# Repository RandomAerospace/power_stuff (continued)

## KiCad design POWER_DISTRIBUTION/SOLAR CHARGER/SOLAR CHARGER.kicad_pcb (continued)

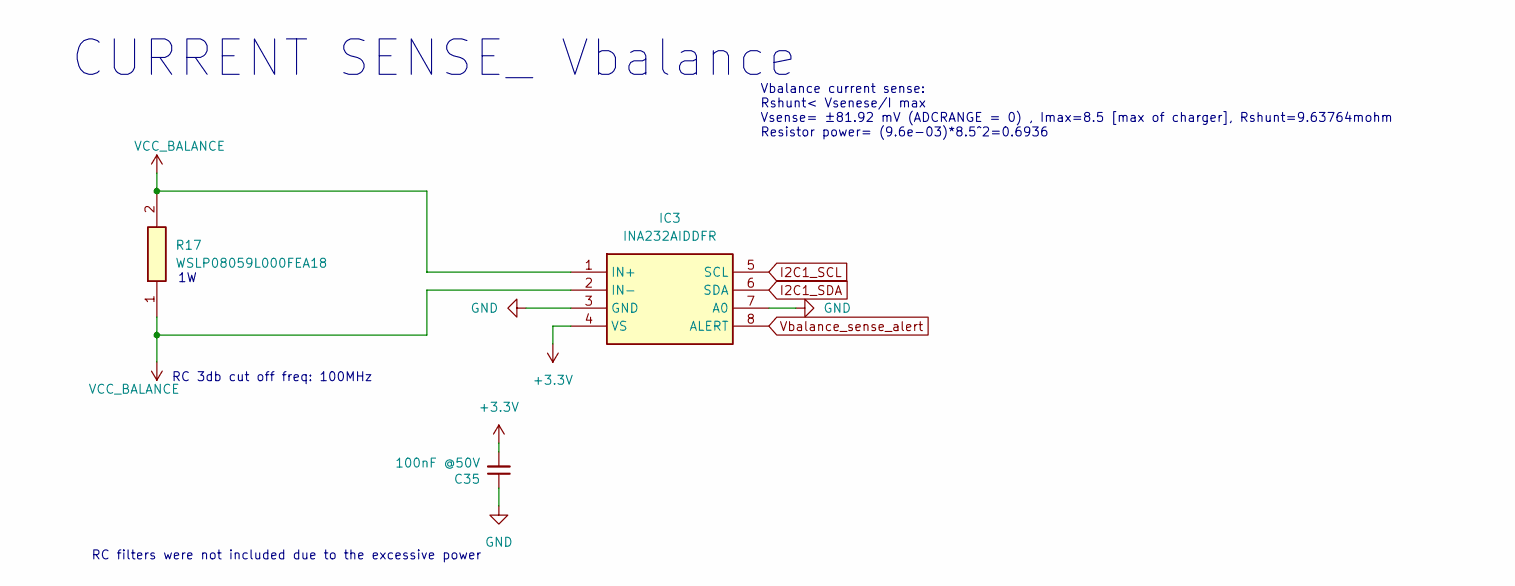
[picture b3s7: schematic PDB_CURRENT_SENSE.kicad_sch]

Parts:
C35: 100nF @50V; C_0402_1005Metric_Pad0.74x0.62mm_HandSolder
IC3: INA232AIDDFR; SOT65P280X110-8N; Mouser Part Number 595-INA232AIDDFR
R17: WSLP08059L000FEA18; RESC2013X58N; Mouser Part Number 71-WSLP08059L000FEA1

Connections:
+3.3V: C35.2, IC3.4 (VS); also elsewhere on the board
GND: C35.1, IC3.3 (GND), IC3.7 (A0); also elsewhere on the board
I2C1_SCL: IC3.5 (SCL); also elsewhere on the board
I2C1_SDA: IC3.6 (SDA); also elsewhere on the board
VCC_BALANCE: IC3.1 (IN+), IC3.2 (IN-), R17.1, R17.2; also elsewhere on the board
Vbalance_sense_alert: IC3.8 (ALERT); also elsewhere on the board

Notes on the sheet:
RC filters were not included due to the excessive power
Vbalance current sense: Rshunt< Vsenese/I max Vsense= ±81.92 mV (ADCRANGE = 0) , Imax=8.5 [max of charger], Rshunt=9.63764mohm Resistor power= (9.6e-03)*8.5^2=0.6936
RC 3db cut off freq: 100MHz
CURRENT SENSE_ Vbalance

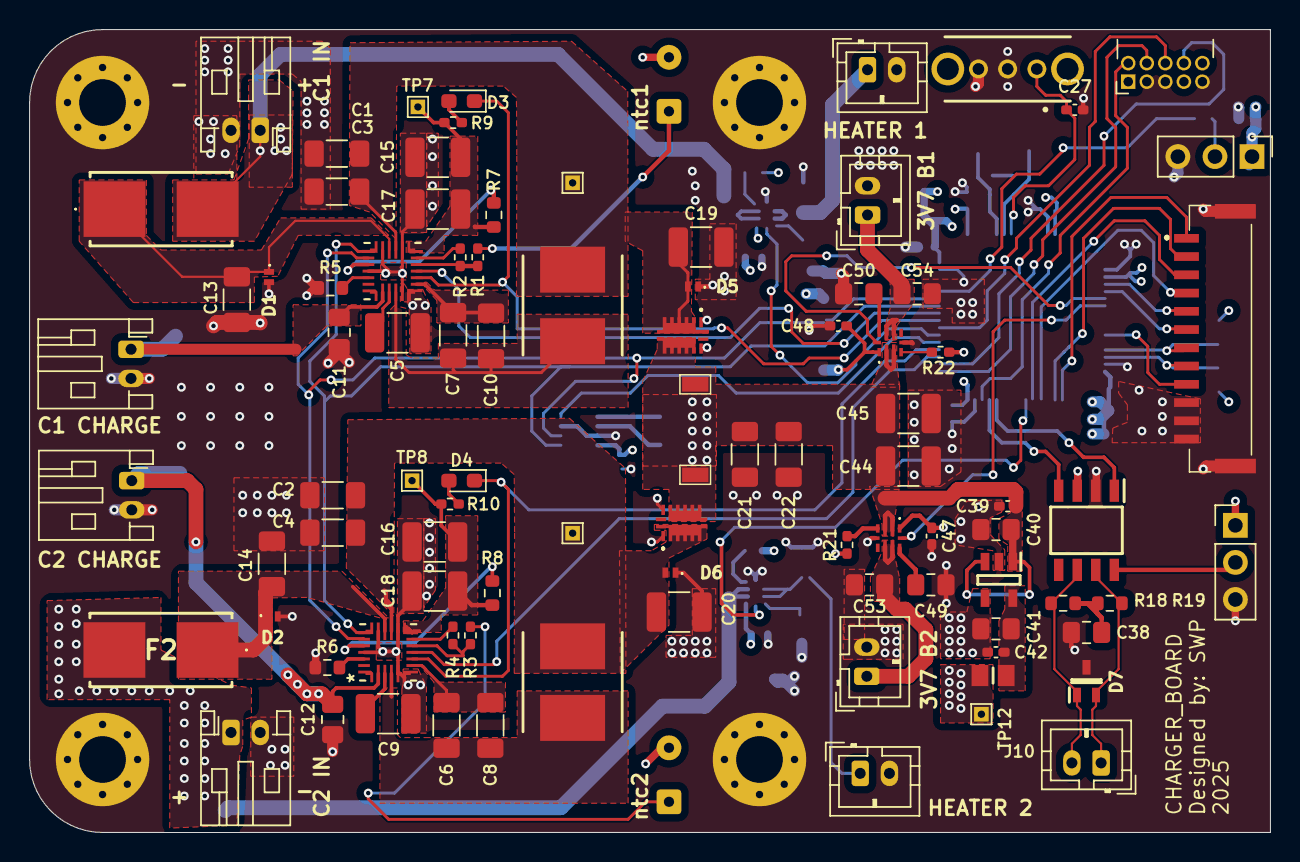
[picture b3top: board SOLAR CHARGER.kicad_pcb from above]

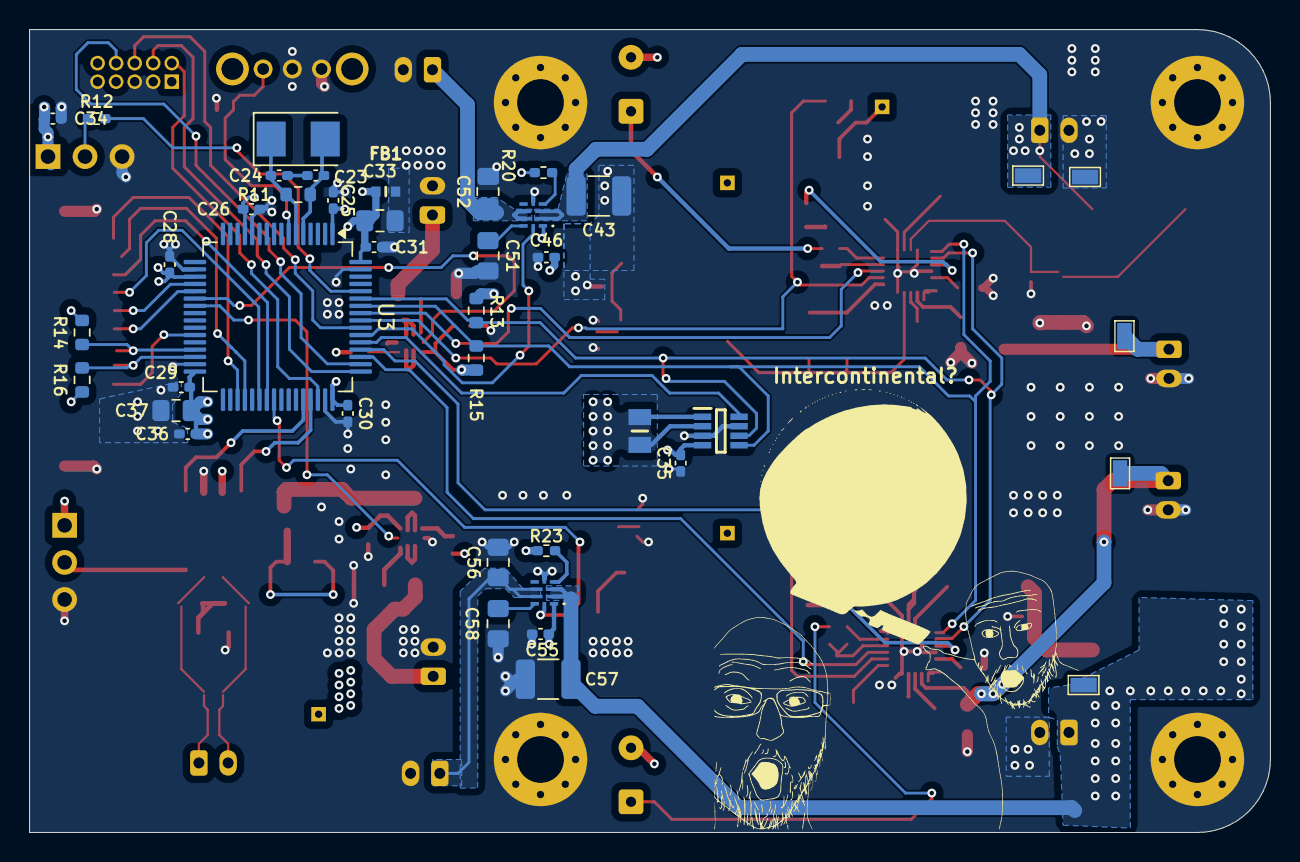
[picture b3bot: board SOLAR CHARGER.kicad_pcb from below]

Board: 4 copper layers, 85.0 x 55.0 mm, 138 parts (41 on the bottom side), 81 nets.

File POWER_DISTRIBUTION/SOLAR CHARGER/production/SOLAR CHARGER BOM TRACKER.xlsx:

Reference | Value | Footprint | Datasheet | Qty | DNP | Exclude from BOM | Exclude from Board
R7,R8 | CRCW0603100KFKEA | Resistor_SMD:R_0603_1608Metric | 100K | 2
R1,R2,R3,R4,R9,R10,R12,R20,R21,R22,R23 | CRCW040210K0FKED | Resistor_SMD:R_0402_1005Metric_Pad0.72x0.64mm_HandSolder | 10k | 11
C23,C24 | GRM1555C1H200GA01D | Capacitor_SMD:C_0402_1005Metric_Pad0.74x0.62mm_HandSolder | 20p | 2
C25,C26,C27,C28,C29,C30,C31,C34,C35,C36,C39,C42,C46,C47,C48,C55 | GRM155R61H104KE19J | Capacitor_SMD:C_0402_1005Metric_Pad0.74x0.62mm_HandSolder | 100nF @50V | 16
C1,C2,C3,C4,C6,C7,C8,C10,C13,C14,C21,C22 | GRM31CR61C476ME44L | Capacitor_SMD:C_1206_3216Metric_Pad1.33x1.80mm_HandSolder | 47uF @16VDC | 12
C5,C9,C15,C16,C17,C18,C19,C20,C43,C44,C45,C57 | GRM32EC72A106KE05L | Capacitor_SMD:C_1210_3225Metric_Pad1.33x2.70mm_HandSolder | 10uF @50V | 12
C11,C12,C33,C37,C38,C40,C41,C49,C50,C51,C52,C53,C54,C56,C58 | GRT21BR71H105KE01K | Capacitor_SMD:C_0805_2012Metric_Pad1.18x1.45mm_HandSolder | 1uF @50V | 15
J2 | Conn_ARM_JTAG_SWD_10 | Connector_PinHeader_1.27mm:PinHeader_2x05_P1.27mm_Horizontal | http://infocenter.arm.com/help/topic/com.arm.doc.ddi0314h/DD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 | 1
J18 | BM12B-GHS-TBT_LF__SN_ | samac_sys:BM12BGHSTBTLFSN | http://www.jst-mfg.com/product/pdf/eng/eGH.pdf | 1
FB1 | BLM18AG601SN1D | samac_sys:BLM18SP221SN1B | http://www.murata.com/~/media/webrenewal/support/library/cat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 | 1
IC4 | SN65HVD233QDRQ1 | samac_sys:SOIC127P600X175-8N | http://www.ti.com/lit/gpn/sn65hvd233-q1 | 1
PS1 | TLV75733PDBVR | samac_sys:SOT95P280X145-5N | http://www.ti.com/lit/gpn/tlv757p | 1
D7 | PESD2CANFD24V-UX | samac_sys:SOT65P210X110-3N | https://assets.nexperia.com/documents/data-sheet/PESD2CANFD2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 | 1
D1,D2,D5,D6 | PTVS3V3D1BALYL | samac_sys:PESD5V0S1BL315 | https://assets.nexperia.com/documents/data-sheet/PTVS3V3D1BAL.pdf | 4
FB2 | BLM21PG221SN1D | samac_sys:BEADC2012X105N | https://datasheet.datasheetarchive.com/originals/dk/DKDS-31/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 | 1
L1,L2 | SRR6838A-1R0Y | samac_sys:INDPM6868X420N | https://g.componentsearchengine.com/Datasheets/0/20314705.pdf | 2
IC1,IC2 | LTC4451AV#TRMPBF | samac_sys:LTC4451AVTRMPBF | https://www.analog.com/media/en/technical-documentation/data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 | 2
S1 | OS102011MA1QN1 | samac_sys:OS102011MA1QN1 | https://www.ckswitches.com/media/1428/os.pdf | 1
F1,F2 | 0154005.DR | samac_sys:0154005DR | https://www.littelfuse.com/~/media/electronics/datasheets/fu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 | 2
TP9,TP10,TP11,TP14,TP15,TP16,TP17 | S2761-46R | samac_sys:S276146R | https://www.mouser.fr/ProductDetail/Harwin/S2761-46R?qs=Daxo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 | 7
U3 | STM32F103RGTx | Package_QFP:LQFP-64_10x10mm_P0.5mm | https://www.st.com/resource/en/datasheet/stm32f103rg.pdf | 1
IC3 | INA232AIDDFR | samac_sys:SOT65P280X110-8N | https://www.ti.com/lit/ds/symlink/ina232.pdf?ts=167813500520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 | 1
IC5,IC6,IC7,IC8 | TPS22997RYZR | samac_sys:TPS22997RYZR | https://www.ti.com/lit/gpn/tps22997?HQS=ti-null-null-sf-df-p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 | 4
R17 | WSLP08059L000FEA18 | samac_sys:RESC2013X58N | https://www.vishay.com/docs/30298/wslp18.pdf | 1
U1,U2 | MP2731GQC-0000-P | MP2731:QFN-26_MP2731 |  | 2
R18,R19 | RK73H1HRTTCM60R4F | Resistor_SMD:R_0603_1608Metric |  | 2
Y1 | X50328MSB2GI | Crystal:Crystal_SMD_5032-2Pin_5.0x3.2mm |  | 1
D3,D4 | LED | LED_SMD:LED_0603_1608Metric_Pad1.05x0.95mm_HandSolder | ~ | 2
H1,H2,H3,H4 | MountingHole_Pad | MountingHole:MountingHole_3.2mm_M3_Pad_Via | ~ | 4 |  | Excluded from BOM
J1 | Conn_01x03_Socket | Connector_PinHeader_2.54mm:PinHeader_1x03_P2.54mm_Vertical | ~ | 1
J3,J5,J6,J7 | Conn_01x02 | Connector_JST:JST_PH_S2B-PH-K_1x02_P2.00mm_Horizontal | ~ | 4
J8,J9 | Conn_01x02 | Connector_Wire:SolderWire-0.127sqmm_1x02_P3.7mm_D0.48mm_OD1mm | ~ | 2
J10,J12,J13,J14,J15 | Conn_01x02 | Connector_JST:JST_PH_B2B-PH-K_1x02_P2.00mm_Vertical | ~ | 5
J11 | Conn_01x03 | Connector_PinHeader_2.54mm:PinHeader_1x03_P2.54mm_Vertical | ~ | 1
R5,R6 | 20K | Resistor_SMD:R_0603_1608Metric | ~ | 2
R11 | 1M | Resistor_SMD:R_0603_1608Metric | ~ | 1
R13,R14,R15,R16 | 2.4k | Resistor_SMD:R_0603_1608Metric | ~ | 4
TP1,TP2,TP7,TP8,TP12 | TestPoint_Alt | TestPoint:TestPoint_THTPad_1.0x1.0mm_Drill0.5mm | ~ | 5
TP3,TP4,TP5,TP6 | TestPoint_Alt | TestPoint:TestPoint_THTPad_1.0x1.0mm_Drill0.5mm | ~ | 4 | DNP | Excluded from BOM | Excluded from board

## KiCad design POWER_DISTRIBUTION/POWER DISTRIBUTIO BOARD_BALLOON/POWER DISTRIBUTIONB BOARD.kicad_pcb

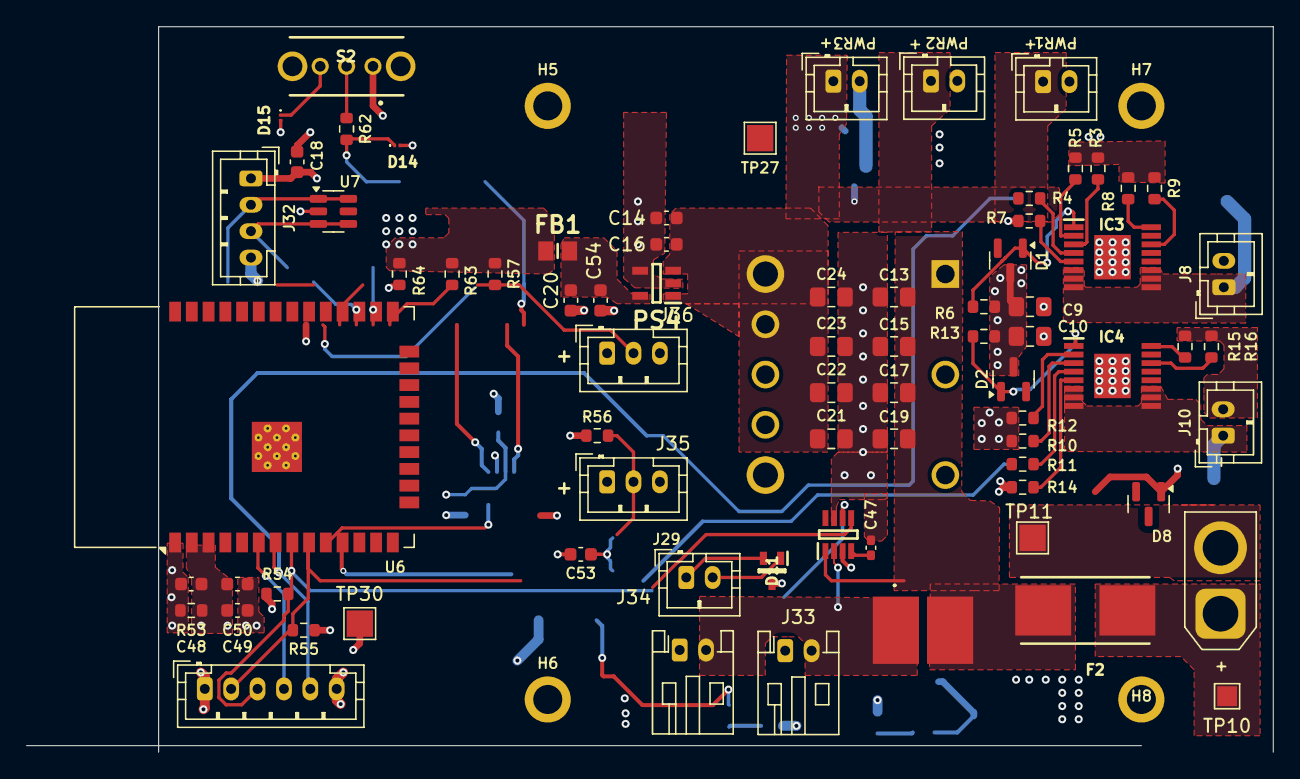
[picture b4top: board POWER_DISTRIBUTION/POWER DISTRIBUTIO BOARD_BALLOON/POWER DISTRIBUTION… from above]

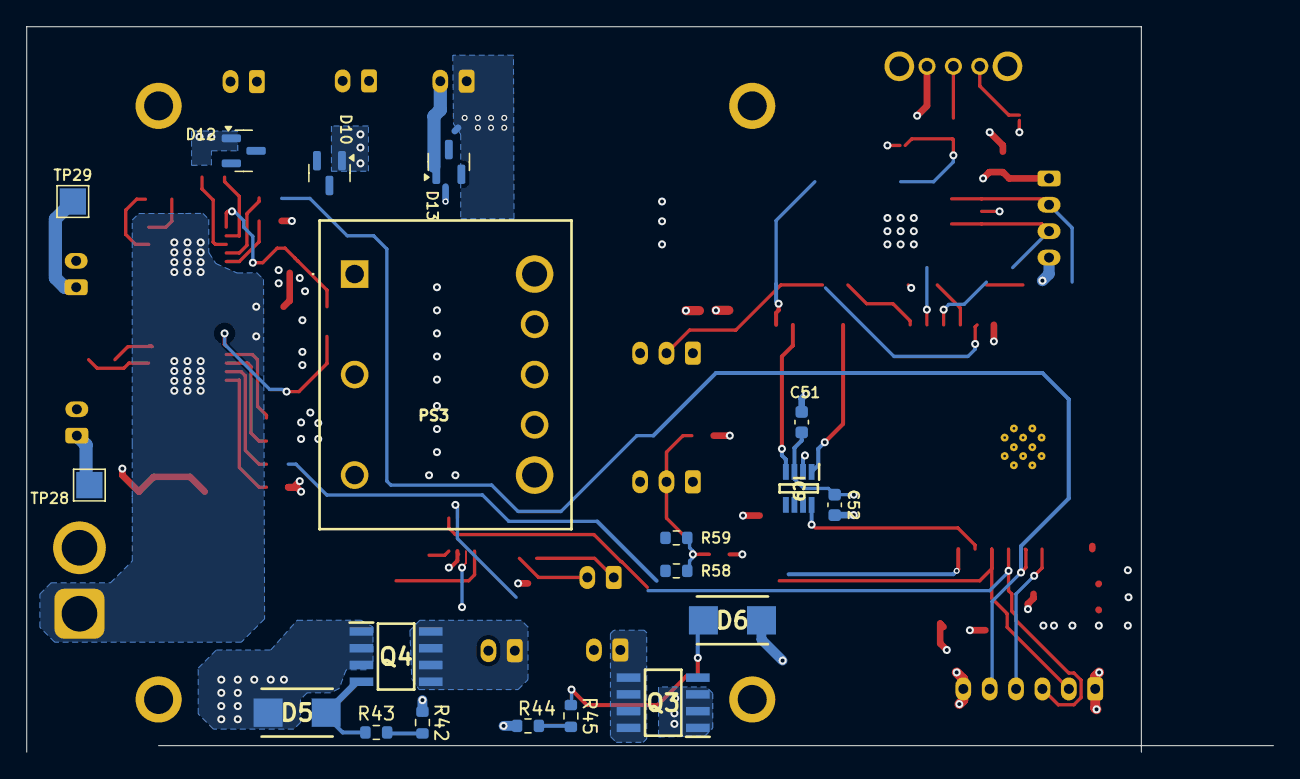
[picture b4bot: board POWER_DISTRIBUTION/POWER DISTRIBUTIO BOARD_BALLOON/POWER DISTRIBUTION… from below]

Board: 4 copper layers, 94.5 x 55.0 mm, 98 parts (19 on the bottom side), 48 nets.

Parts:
C9, C10: 1uF @50V; C_0805_2012Metric_Pad1.18x1.45mm_HandSolder
C13, C15, C17, C19, C21, C22, C23, C24: 10uF@16V; C_0805_2012Metric_Pad1.18x1.45mm_HandSolder
C14, C20, C50, C52: 1uF; C_0603_1608Metric
C16, C18, C48, C49, C51, C54: 100nF; C_0603_1608Metric
C47: 100nF @50V; C_0402_1005Metric_Pad0.74x0.62mm_HandSolder
C53: 4.7nF; C_0603_1608Metric
D1, D2, D8, D10, D12, D13: BAS21; SOT-23
D5, D6: SMBJ12CA; DIONM5436X244N
D11: PESD2CANFD24V-UX; SOT65P210X110-3N
D14, D15: PESD3V3Z1BCSFYL; PMEG3005AESFYL
F2: 0154005.DRL; 0154005DRL
FB1: BLM21PG221SN1D; BEADC2012X105N
H5, H6, H7, H8: MountingHole_Pad; MountingHole_2.2mm_M2_ISO7380_Pad
IC3, IC4: TPS1HB08BQPWPRQ1; SOP65P640X120-17N
IC8: INA232AIDDFR; SOT65P280X110-8N
IC9: TCAN1044VDDFR; SOT65P280X110-8N
J8, J9, J10, J29, J30, J31: Conn_01x02; JST_PH_B2B-PH-K_1x02_P2.00mm_Vertical
J11: Conn_01x02; AMASS_XT30U-F_1x02_P5.0mm_Vertical
J28: Conn_01x06; JST_PH_B6B-PH-K_1x06_P2.00mm_Vertical
J32: Conn_01x04; JST_PH_B4B-PH-K_1x04_P2.00mm_Vertical
J33, J34: Conn_01x02; JST_PH_S2B-PH-K_1x02_P2.00mm_Horizontal
J35, J36: Conn_01x03; JST_PH_B3B-PH-K_1x03_P2.00mm_Vertical
PS3: RPMA5.0-4.5_OF; RPMA5045OF
PS4: TLV75733PDBVR; SOT95P280X145-5N
Q3, Q4: RSS070N05HZGTB; SOIC127P600X175-8N
R3, R4, R8, R9, R10, R11, R15, R16: 15k; R_0603_1608Metric
R5, R12, R62: 1K; R_0603_1608Metric
R6, R13: 4.7k; R_0603_1608Metric
R7, R14: 13.3k; R_0603_1608Metric
R42, R44: 10M; R_0603_1608Metric
R43, R45: 2k; R_0603_1608Metric
R52: WSHM28186L800FEA; WSHM2818R0330FEB
R53: 10K; R_0603_1608Metric
R54, R55, R63, R64: 2K4; R_0603_1608Metric
R56, R57: 4k7; R_0603_1608Metric
R58, R59: 60; R_0603_1608Metric
S2: OS102011MA1QN1
TP10: S2761-46R; TestPoint_Pad_1.5x1.5mm
TP11, TP27, TP28, TP29, TP30: S2761-46R; TestPoint_Pad_2.0x2.0mm
U6: ESP32-WROOM-32E; ESP32-WROOM-32D
U7: USBLC6-2SC6; SOT-23-6

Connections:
12V_BUS1: IC4.6 (VOUT_1), IC4.7 (VOUT_2), IC4.8 (VOUT_3), IC4.9 (VOUT_4), IC4.10 (VOUT_5), IC4.11 (VOUT_6), J10.1, TP28.1
12V_BUS2: IC3.6 (VOUT_1), IC3.7 (VOUT_2), IC3.8 (VOUT_3), IC3.9 (VOUT_4), IC3.10 (VOUT_5), IC3.11 (VOUT_6), J8.1, TP29.1
+3.3V: C47.2, IC8.4 (VS)
+3V3: C18.2, C48.2, C49.1, C50.1, C51.1, C52.1, D15.1 (K1), FB1.2, IC9.3 (VCC), J28.1, J32.1, J35.1, J36.1, R53.2, R54.1, R55.1, R56.1, R57.1, R63.1, R64.1, S2.3, TP30.1, U6.2 (VDD), U6.3 (EN), U7.5 (VBUS)
+5V0: C14.1, C16.1, C21.2, C22.2, C23.2, C24.2, D10.3 (K), D12.3 (K), D13.3 (K), J9.1, J30.1, J31.1, PS3.7 (+SENSE), PS3.8 (+VOUT), PS4.1 (IN), PS4.3 (EN), TP27.1
BOOT: D14.1 (K1), R62.2, U6.25 (IO0)
CAN+: D11.2 (K2), IC9.7 (CANH), J29.1, R58.2
CAN-: D11.1 (K1), IC9.6 (CANL), J29.2, R59.1
CAN_RX: IC9.4 (RXD), U6.26 (IO4)
CAN_TX: IC9.1 (TXD), U6.29 (IO5)
CUTTER_EN: J28.4, U6.6 (IO34)
GND: C9.1, C10.1, C13.1, C14.2, C15.1, C16.2, C17.1, C18.1, C19.1, C20.2, C21.1, C22.1, C23.1, C24.1, C47.1, C48.1, C49.2, C50.2, C51.2, C52.2, C53.2, C54.2, D1.3 (K), D2.3 (K), D5.1, D6.1, D8.1 (A), D10.1 (A), D11.3 (CC), D12.1 (A), D13.1 (A), D14.2 (K2), D15.2 (K2), H5.1, H6.1, H7.1, H8.1, IC8.3 (GND), IC8.7 (A0), IC9.2 (GND), IC9.8 (STB), J8.2, J9.2, J10.2, J11.2, J28.6, J30.2, J31.2, J32.4, J35.3, J36.3, PS3.3 (-VIN), PS3.4 (-VOUT), PS4.2 (GND), PS4.4 (NC), Q3.1 (SOURCE_1), Q3.2 (SOURCE_2), Q3.3 (SOURCE_3), Q4.1 (SOURCE_1), Q4.2 (SOURCE_2), Q4.3 (SOURCE_3), R3.1, R5.1, R6.2, R7.1, R8.2, R9.2, R10.1, R12.1, R13.2, R14.1, R15.2, R16.2, R42.1, R44.1, R53.1, S2.1, TP11.1, U6.1 (GND), U6.15 (GND), U6.38 (GND), U6.39 (GND), U7.2 (GND)
GPIO1_EN: R42.2, R43.2
GPIO2_EN: R44.2, R45.2
HEATER_EN: R11.1, U6.11 (IO26)
I2C2_SDA: IC8.6 (SDA), J28.3, R54.2, U6.8 (IO32)
I2C2_SDL: IC8.5 (SCL), J28.2, R55.2, U6.9 (IO33)
I2C_SDA: R63.2, U6.33 (IO21)
I2C_SDL: R64.2, U6.36 (IO22)
unnamed: C53.1, R58.1, R59.2
unnamed: D1.1 (A), IC3.1 (GND), R6.1
unnamed: D2.1 (A), IC4.1 (GND), R13.1
unnamed: IC3.16 (DIA_EN), R8.1
unnamed: IC3.4 (EN), R4.2
unnamed: IC3.5 (ILIM), R7.2
unnamed: IC3.3 (LATCH), R3.2
unnamed: IC3.14 (SEL1), R9.1
unnamed: IC3.2 (SNS), R5.2
unnamed: IC4.16 (DIA_EN), R15.1
unnamed: IC4.4 (EN), R11.2
unnamed: IC4.5 (ILIM), R14.2
unnamed: IC4.3 (LATCH), R10.2
unnamed: IC4.14 (SEL1), R16.1
unnamed: IC4.2 (SNS), R12.2
unnamed: C20.1, C54.1, FB1.1, PS4.5 (OUT)
unnamed: D6.2, Q3.4 (GATE), R45.1
unnamed: D5.2, Q4.4 (GATE), R43.1
unnamed: R62.1, S2.2
PGM_RX: J32.2, U6.35 (TXD0/IO1), U7.1 (I/O1), U7.6 (I/O1)
PGM_TX: J32.3, U6.34 (RXD0/IO3), U7.3 (I/O2), U7.4 (I/O2)
PYR_1: J33.1, Q4.5 (DRAIN_1), Q4.6 (DRAIN_2), Q4.7 (DRAIN_3), Q4.8 (DRAIN_4)
PYR_2: J34.1, Q3.5 (DRAIN_1), Q3.6 (DRAIN_2), Q3.7 (DRAIN_3), Q3.8 (DRAIN_4)
VBAT+: C9.2, C10.2, D8.3 (K), F2.1, IC3.17 (VBB), IC4.17 (VBB), J11.1, TP10.1
VBAT_Fused: C13.2, C15.2, C17.2, C19.2, F2.2, IC8.1 (IN+), PS3.1 (+VIN), R52.2
VBAT_Fused_OUT: IC8.2 (IN-), J33.2, J34.2, R52.1
VTX_EN: J28.5, R4.1, U6.7 (IO35)
onewire1: J35.2, R56.2, U6.10 (IO25)
onewire2: J36.2, R57.2, U6.37 (IO23)

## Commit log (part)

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2026-02-23 added everytrhing
2026-03-19 commit after disaster
2026-06-28 addition of UREX pDB
2026-06-28 CONFIGURED LIBARY PATHS FOR UREX_PDB
2026-06-29 FIXED LIBRARY
